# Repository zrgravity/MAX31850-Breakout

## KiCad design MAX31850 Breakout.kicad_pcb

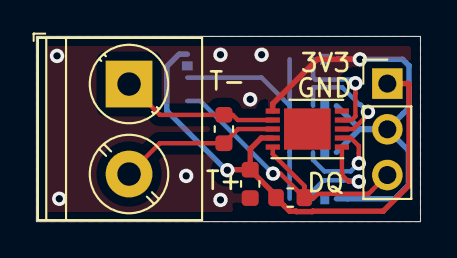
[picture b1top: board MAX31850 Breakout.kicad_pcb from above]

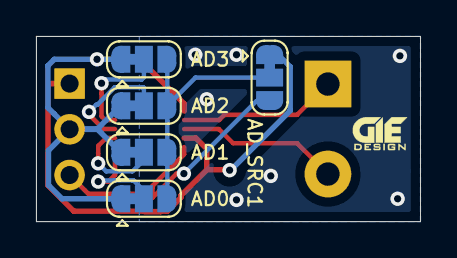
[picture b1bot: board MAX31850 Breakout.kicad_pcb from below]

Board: 2 copper layers, 21.3 x 10.3 mm, 11 parts (5 on the bottom side), 10 nets.

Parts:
AD0, AD1, AD2, AD3: SolderJumper_3_Bridged12; SolderJumper-3_P1.3mm_Bridged12_RoundedPad1.0x1.5mm
AD_SRC1: SolderJumper_3_Bridged12; SolderJumper-3_P1.3mm_Bridged12_RoundedPad1.0x1.5mm
C1: 10nF; C_0603_1608Metric
C2: 0.1uF; C_0603_1608Metric
J1: Conn_01x02; TerminalBlock_Phoenix_PT-1,5-2-5.0-H_1x02_P5.00mm_Horizontal
J2: Conn_01x03; PinHeader_1x03_P2.54mm_Vertical
R1: DNP_4.7k; R_0603_1608Metric
U1: MAX31850KATB; TDFN-10-1EP_3x4mm_P0.5mm_EP1.75x2.7mm

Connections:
+3V3: AD_SRC1.1, C2.1, J2.1, R1.1, U1.4
/AD0: AD0.2, U1.6
/AD1: AD1.2, U1.7
/AD2: AD2.2, U1.8
/AD3: AD3.2, U1.9
/DQ: AD_SRC1.3, J2.3, R1.2, U1.5
/T+: C1.1, J1.2, U1.3
/T-: C1.2, J1.1, U1.2
GND: AD0.1, AD1.1, AD2.1, AD3.1, C2.2, J2.2, U1.1
unnamed: AD0.3, AD1.3, AD2.3, AD3.3, AD_SRC1.2

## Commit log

2020-03-09 Create kicad project, library, copy part
    Part needs to be updated and fixed
2020-03-09 Update component and footprint
2020-03-09 Add datasheet
2020-03-19 Create schematic
2020-03-19 Move library and datasheet folders around
    See https://hackaday.com/2017/05/18/kicad-best-practises-library-management/ for more info
2020-03-19 Assign footprints
2020-03-20 Update Jumper component, label all nets
2020-03-20 Update project library
2020-03-20 Layout and Route PCB
2020-03-20 Add dimensions
2020-03-20 Add gerbers
    Order from https://oshpark.com/shared_projects/sVVwuo6v
2020-03-20 Replace footprints with local copy
